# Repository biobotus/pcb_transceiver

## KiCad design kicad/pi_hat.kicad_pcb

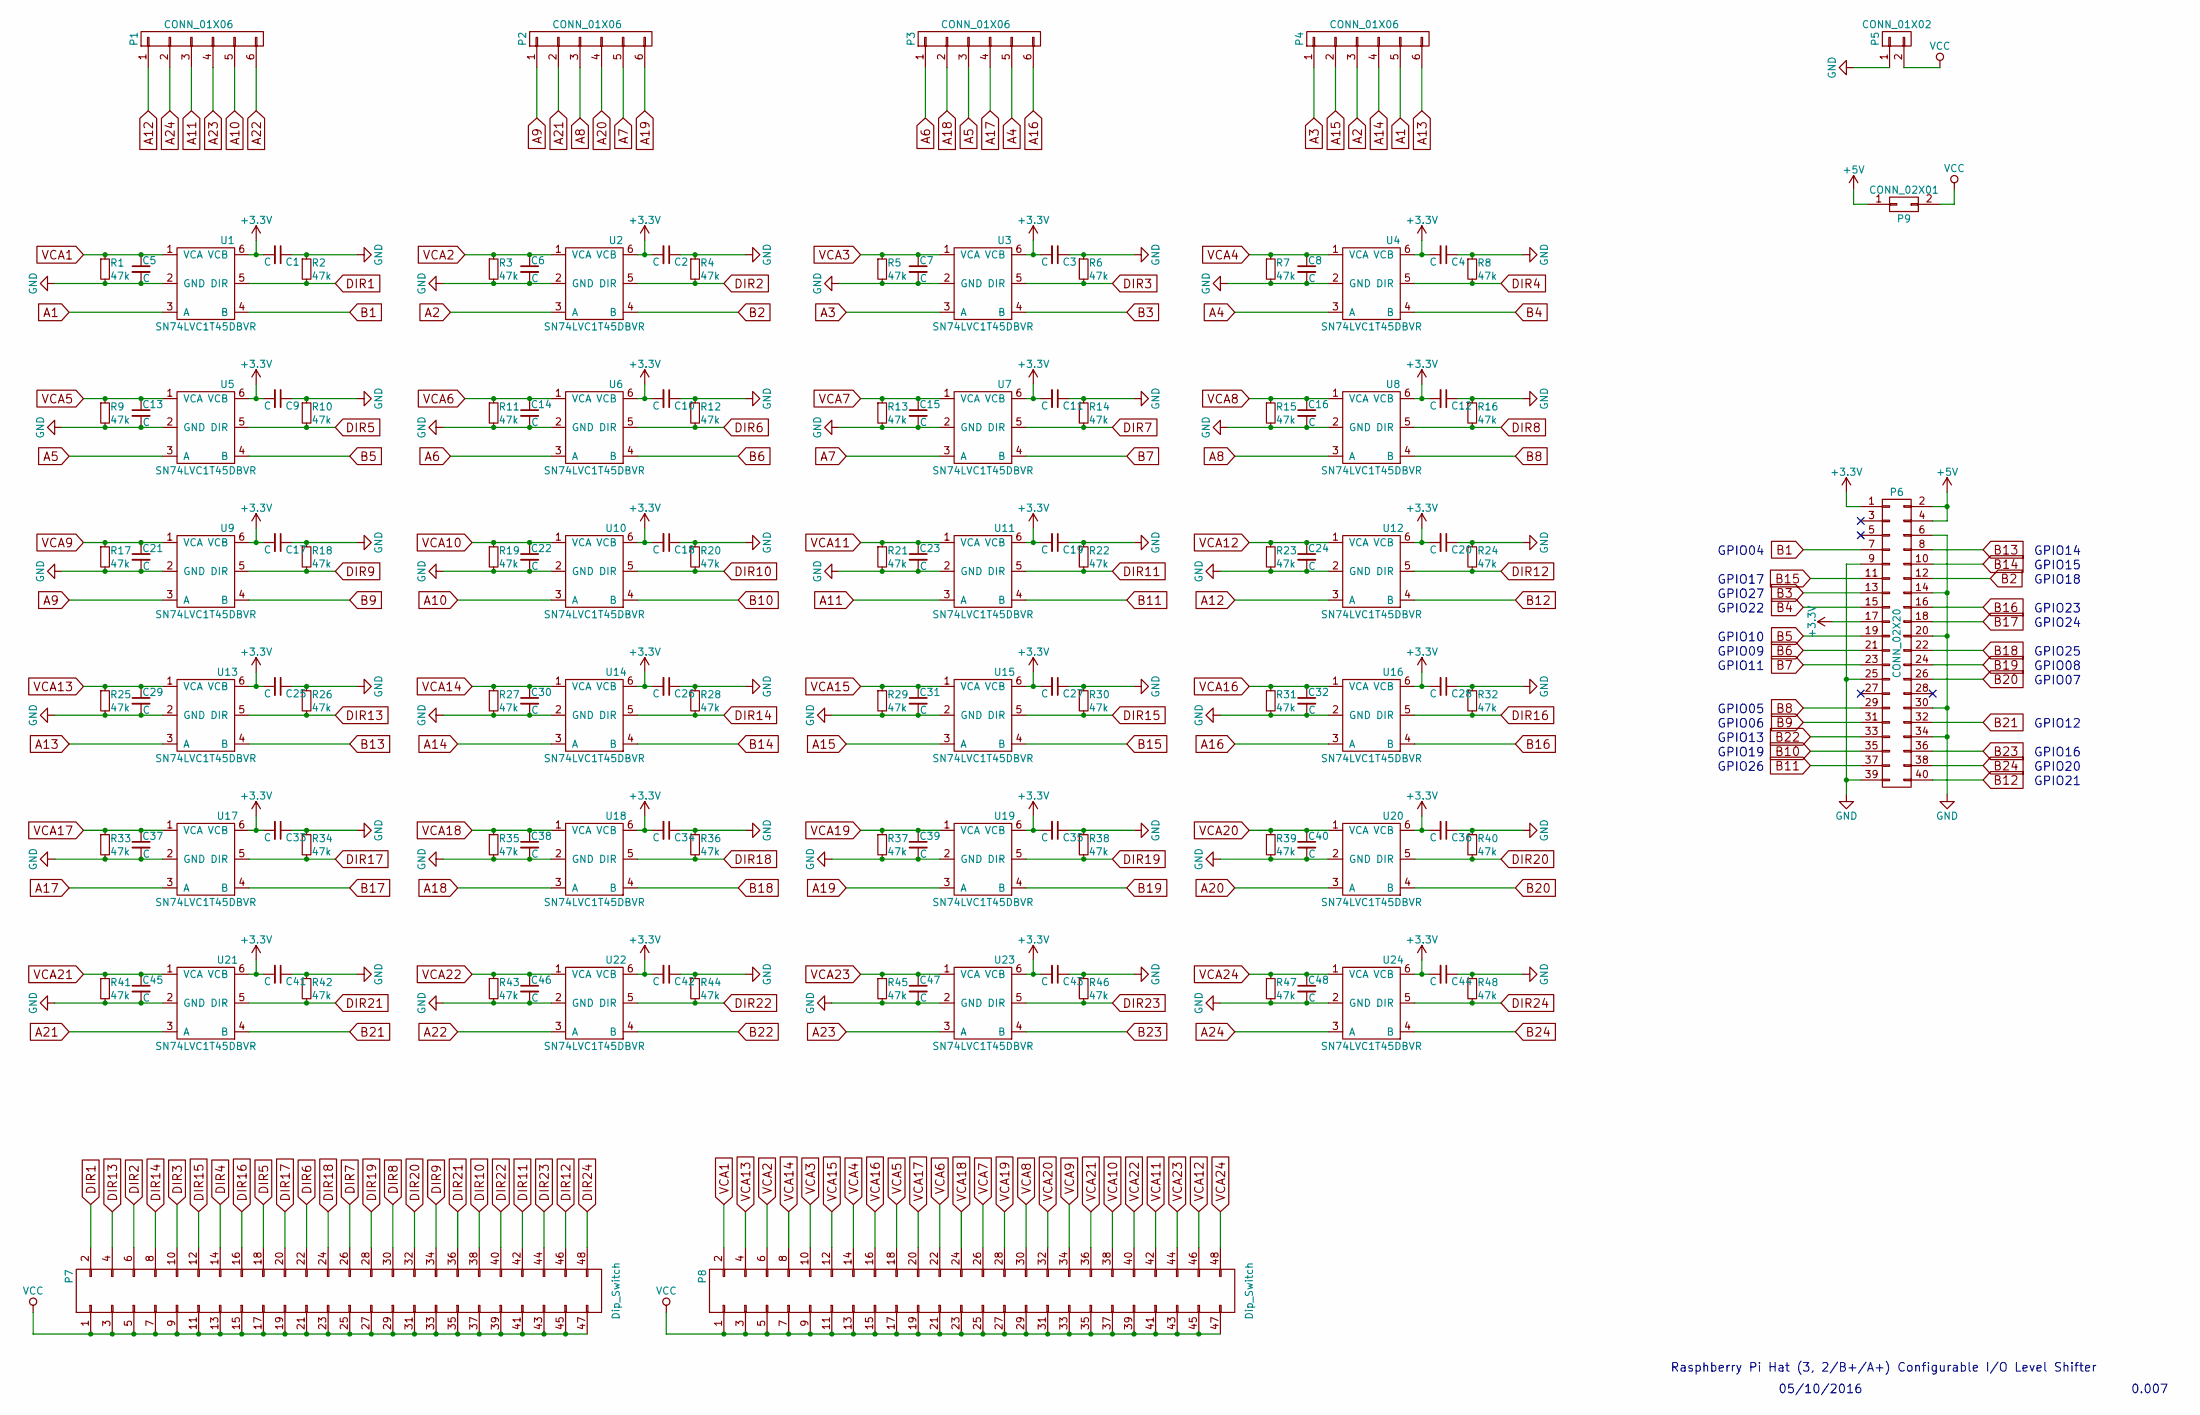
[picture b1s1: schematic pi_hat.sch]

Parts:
C1, C2, C3, C4, C5, C6, C7, C8, C9, C10, C11, C12, C13, C14, C15, C16, C17, C18, C19, C20, C21, C22, C23, C24, C25, C26, C27, C28, C29, C30, C31, C32, C33, C34, C35, C36, C37, C38, C39, C40, C41, C42, C43, C44, C45, C46, C47, C48: C; 0402(1005m)
P1, P2, P3, P4: CONN_01X06; Header_6X1
P5: CONN_01X02; Header_2X1
P6: CONN_02X20; Staking-Header
P7, P8: Dip_Switch; M50-3501242
P9: CONN_02X01; Heade_2_jumper
R1, R2, R3, R4, R5, R6, R7, R8, R9, R10, R11, R12, R13, R14, R15, R16, R17, R18, R19, R20, R21, R22, R23, R24, R25, R26, R27, R28, R29, R30, R31, R32, R33, R34, R35, R36, R37, R38, R39, R40, R41, R42, R43, R44, R45, R46, R47, R48: 47k; 0402(1005m)
U1, U2, U3, U4, U5, U6, U7, U8, U9, U10, U11, U12, U13, U14, U15, U16, U17, U18, U19, U20, U21, U22, U23, U24: SN74LVC1T45DBVR; SOT-23-6

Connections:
+3V3: C1.2, C2.2, C3.2, C4.2, C9.2, C10.2, C11.2, C12.2, C17.2, C18.2, C19.2, C20.2, C25.2, C26.2, C27.2, C28.2, C33.2, C34.2, C35.2, C36.2, C41.2, C42.2, C43.2, C44.2, P6.1, P6.17, U1.6 (VCB), U2.6 (VCB), U3.6 (VCB), U4.6 (VCB), U5.6 (VCB), U6.6 (VCB), U7.6 (VCB), U8.6 (VCB), U9.6 (VCB), U10.6 (VCB), U11.6 (VCB), U12.6 (VCB), U13.6 (VCB), U14.6 (VCB), U15.6 (VCB), U16.6 (VCB), U17.6 (VCB), U18.6 (VCB), U19.6 (VCB), U20.6 (VCB), U21.6 (VCB), U22.6 (VCB), U23.6 (VCB), U24.6 (VCB)
+5V: P6.2, P6.4, P9.1
A1: P4.5, U1.3 (A)
A2: P4.3, U2.3 (A)
A3: P4.1, U3.3 (A)
A4: P3.5, U4.3 (A)
A5: P3.3, U5.3 (A)
A6: P3.1, U6.3 (A)
A7: P2.5, U7.3 (A)
A8: P2.3, U8.3 (A)
A9: P2.1, U9.3 (A)
A10: P1.5, U10.3 (A)
A11: P1.3, U11.3 (A)
A12: P1.1, U12.3 (A)
A13: P4.6, U13.3 (A)
A14: P4.4, U14.3 (A)
A15: P4.2, U15.3 (A)
A16: P3.6, U16.3 (A)
A17: P3.4, U17.3 (A)
A18: P3.2, U18.3 (A)
A19: P2.6, U19.3 (A)
A20: P2.4, U20.3 (A)
A21: P2.2, U21.3 (A)
A22: P1.6, U22.3 (A)
A23: P1.4, U23.3 (A)
A24: P1.2, U24.3 (A)
B1: P6.7, U1.4 (B)
B2: P6.12, U2.4 (B)
B3: P6.13, U3.4 (B)
B4: P6.15, U4.4 (B)
B5: P6.19, U5.4 (B)
B6: P6.21, U6.4 (B)
B7: P6.23, U7.4 (B)
B8: P6.29, U8.4 (B)
B9: P6.31, U9.4 (B)
B10: P6.35, U10.4 (B)
B11: P6.37, U11.4 (B)
B12: P6.40, U12.4 (B)
B13: P6.8, U13.4 (B)
B14: P6.10, U14.4 (B)
B15: P6.11, U15.4 (B)
B16: P6.16, U16.4 (B)
B17: P6.18, U17.4 (B)
B18: P6.22, U18.4 (B)
B19: P6.24, U19.4 (B)
B20: P6.26, U20.4 (B)
B21: P6.32, U21.4 (B)
B22: P6.33, U22.4 (B)
B23: P6.36, U23.4 (B)
B24: P6.38, U24.4 (B)
DIR1: P7.2, R2.2, U1.5 (DIR)
DIR2: P7.6, R4.2, U2.5 (DIR)
DIR3: P7.10, R6.2, U3.5 (DIR)
DIR4: P7.14, R8.2, U4.5 (DIR)
DIR5: P7.18, R10.2, U5.5 (DIR)
DIR6: P7.22, R12.2, U6.5 (DIR)
DIR7: P7.26 (P2), R14.2, U7.5 (DIR)
DIR8: P7.30 (P6), R16.2, U8.5 (DIR)
DIR9: P7.34 (P10), R18.2, U9.5 (DIR)
DIR10: P7.38 (P14), R20.2, U10.5 (DIR)
DIR11: P7.42 (P18), R22.2, U11.5 (DIR)
DIR12: P7.46 (P22), R24.2, U12.5 (DIR)
DIR13: P7.4, R26.2, U13.5 (DIR)
DIR14: P7.8, R28.2, U14.5 (DIR)
DIR15: P7.12, R30.2, U15.5 (DIR)
DIR16: P7.16, R32.2, U16.5 (DIR)
DIR17: P7.20, R34.2, U17.5 (DIR)
DIR18: P7.24, R36.2, U18.5 (DIR)
DIR19: P7.28 (P4), R38.2, U19.5 (DIR)
DIR20: P7.32 (P8), R40.2, U20.5 (DIR)
DIR21: P7.36 (P12), R42.2, U21.5 (DIR)
DIR22: P7.40 (P16), R44.2, U22.5 (DIR)
DIR23: P7.44 (P20), R46.2, U23.5 (DIR)
DIR24: P7.48 (P24), R48.2, U24.5 (DIR)
GND: C1.1, C2.1, C3.1, C4.1, C5.2, C6.2, C7.2, C8.2, C9.1, C10.1, C11.1, C12.1, C13.2, C14.2, C15.2, C16.2, C17.1, C18.1, C19.1, C20.1, C21.2, C22.2, C23.2, C24.2, C25.1, C26.1, C27.1, C28.1, C29.2, C30.2, C31.2, C32.2, C33.1, C34.1, C35.1, C36.1, C37.2, C38.2, C39.2, C40.2, C41.1, C42.1, C43.1, C44.1, C45.2, C46.2, C47.2, C48.2, P5.1, P6.6, P6.9, P6.14, P6.20, P6.25, P6.30, P6.34, P6.39, R1.2, R2.1, R3.2, R4.1, R5.2, R6.1, R7.2, R8.1, R9.2, R10.1, R11.2, R12.1, R13.2, R14.1, R15.2, R16.1, R17.2, R18.1, R19.2, R20.1, R21.2, R22.1, R23.2, R24.1, R25.2, R26.1, R27.2, R28.1, R29.2, R30.1, R31.2, R32.1, R33.2, R34.1, R35.2, R36.1, R37.2, R38.1, R39.2, R40.1, R41.2, R42.1, R43.2, R44.1, R45.2, R46.1, R47.2, R48.1, U1.2 (GND), U2.2 (GND), U3.2 (GND), U4.2 (GND), U5.2 (GND), U6.2 (GND), U7.2 (GND), U8.2 (GND), U9.2 (GND), U10.2 (GND), U11.2 (GND), U12.2 (GND), U13.2 (GND), U14.2 (GND), U15.2 (GND), U16.2 (GND), U17.2 (GND), U18.2 (GND), U19.2 (GND), U20.2 (GND), U21.2 (GND), U22.2 (GND), U23.2 (GND), U24.2 (GND)
VCA1: C5.1, P8.2, R1.1, U1.1 (VCA)
VCA2: C6.1, P8.6, R3.1, U2.1 (VCA)
VCA3: C7.1, P8.10, R5.1, U3.1 (VCA)
VCA4: C8.1, P8.14, R7.1, U4.1 (VCA)
VCA5: C13.1, P8.18, R9.1, U5.1 (VCA)
VCA6: C14.1, P8.22, R11.1, U6.1 (VCA)
VCA7: C15.1, P8.26 (P2), R13.1, U7.1 (VCA)
VCA8: C16.1, P8.30 (P6), R15.1, U8.1 (VCA)
VCA9: C21.1, P8.34 (P10), R17.1, U9.1 (VCA)
VCA10: C22.1, P8.38 (P14), R19.1, U10.1 (VCA)
VCA11: C23.1, P8.42 (P18), R21.1, U11.1 (VCA)
VCA12: C24.1, P8.46 (P22), R23.1, U12.1 (VCA)
VCA13: C29.1, P8.4, R25.1, U13.1 (VCA)
VCA14: C30.1, P8.8, R27.1, U14.1 (VCA)
VCA15: C31.1, P8.12, R29.1, U15.1 (VCA)
VCA16: C32.1, P8.16, R31.1, U16.1 (VCA)
VCA17: C37.1, P8.20, R33.1, U17.1 (VCA)
VCA18: C38.1, P8.24, R35.1, U18.1 (VCA)
VCA19: C39.1, P8.28 (P4), R37.1, U19.1 (VCA)
VCA20: C40.1, P8.32 (P8), R39.1, U20.1 (VCA)
VCA21: C45.1, P8.36 (P12), R41.1, U21.1 (VCA)
VCA22: C46.1, P8.40 (P16), R43.1, U22.1 (VCA)
VCA23: C47.1, P8.44 (P20), R45.1, U23.1 (VCA)
VCA24: C48.1, P8.48 (P24), R47.1, U24.1 (VCA)
VCC: P5.2, P7.1, P7.3, P7.5, P7.7, P7.9, P7.11, P7.13, P7.15, P7.17, P7.19, P7.21, P7.23, P7.25 (P1), P7.27 (P3), P7.29 (P5), P7.31 (P7), P7.33 (P9), P7.35 (P11), P7.37 (P13), P7.39 (P15), P7.41 (P17), P7.43 (P19), P7.45 (P21), P7.47 (P23), P8.1, P8.3, P8.5, P8.7, P8.9, P8.11, P8.13, P8.15, P8.17, P8.19, P8.21, P8.23, P8.25 (P1), P8.27 (P3), P8.29 (P5), P8.31 (P7), P8.33 (P9), P8.35 (P11), P8.37 (P13), P8.39 (P15), P8.41 (P17), P8.43 (P19), P8.45 (P21), P8.47 (P23), P9.2

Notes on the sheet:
0.007
05/10/2016
Rasphberry Pi Hat (3, 2/B+/A+) Configurable I/O Level Shifter
GPIO04
GPIO17
GPIO27
GPIO22
GPIO10
GPIO09
GPIO11
GPIO05
GPIO06
GPIO13
GPIO19
GPIO26
GPIO14
GPIO15
GPIO18
GPIO23
GPIO24
GPIO25
GPIO08
GPIO07
GPIO12
GPIO16
GPIO20
GPIO21

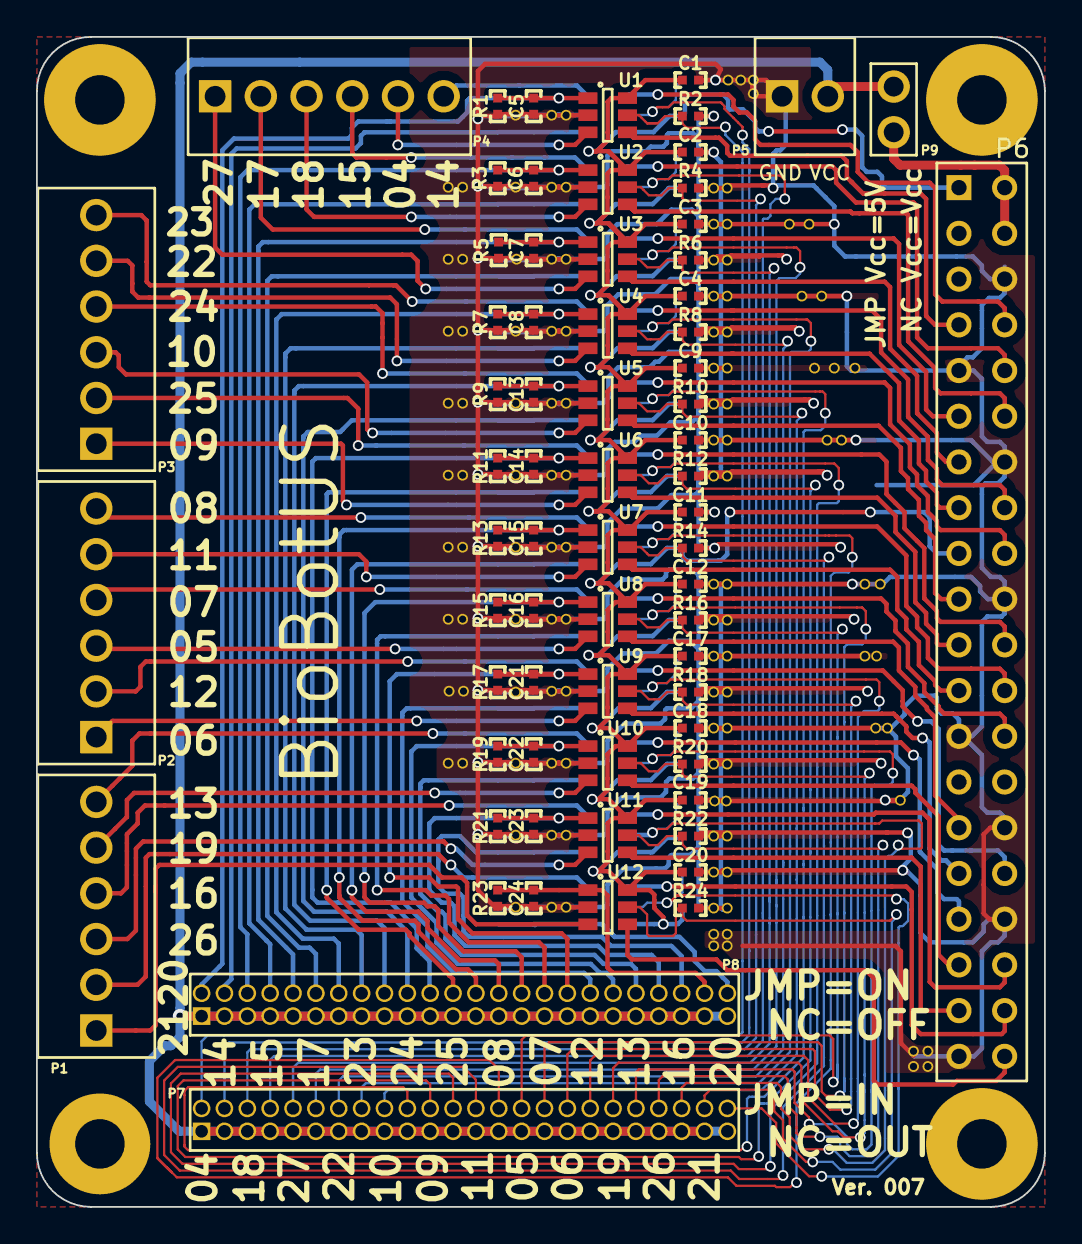
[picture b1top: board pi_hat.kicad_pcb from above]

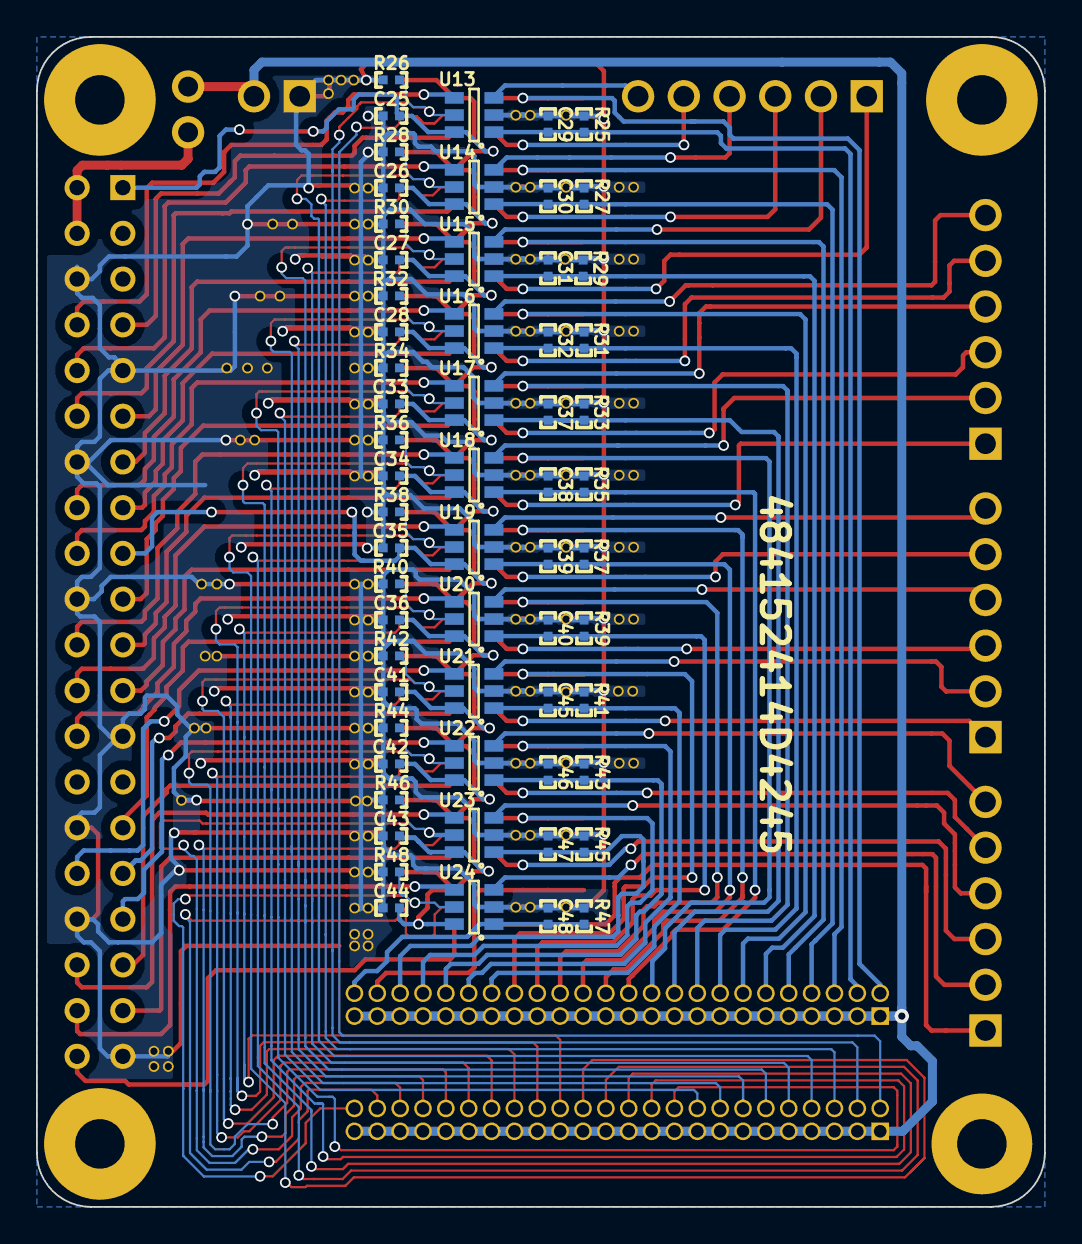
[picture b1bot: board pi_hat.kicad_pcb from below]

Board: 2 copper layers, 56.0 x 65.0 mm, 129 parts (60 on the bottom side), 100 nets.
